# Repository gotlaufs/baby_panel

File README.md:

# baby_panel
Toy panel with a ton of lights and switches

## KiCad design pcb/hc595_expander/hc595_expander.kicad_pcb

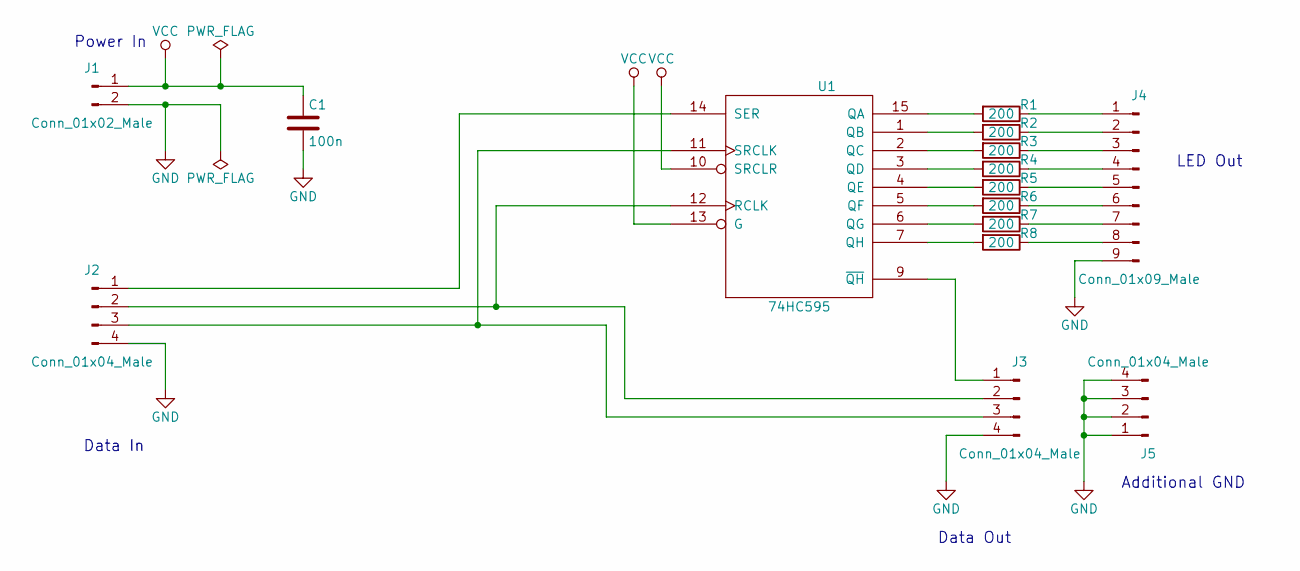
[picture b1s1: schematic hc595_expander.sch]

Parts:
C1: 100n; C_0805_HandSoldering
J1: Conn_01x02_Male; Header_1x02_2.54mm_Oval
J2, J3, J5: Conn_01x04_Male; Header_1x04_2.54mm_Oval
J4: Conn_01x09_Male; Header_1x09_2.54mm_Oval
R1, R2, R3, R4, R5, R6, R7, R8: 200; R_0805_HandSoldering
U1: 74HC595; SOIC-16W_7.5x10.3mm_Pitch1.27mm_HandSoldering

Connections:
GND: C1.2, J1.2, J2.4, J3.4, J4.9, J5.1, J5.2, J5.3, J5.4, U1.8 (GND)
unnamed: J2.1, U1.14 (SER)
unnamed: J2.2, J3.2, U1.12 (RCLK)
unnamed: J2.3, J3.3, U1.11 (SRCLK)
unnamed: J3.1, U1.9 (~QH)
unnamed: J4.1, R1.1
unnamed: J4.2, R2.1
unnamed: J4.3, R3.1
unnamed: J4.4, R4.1
unnamed: J4.5, R5.1
unnamed: J4.6, R6.1
unnamed: J4.7, R7.1
unnamed: J4.8, R8.1
unnamed: R1.2, U1.15 (QA)
unnamed: R2.2, U1.1 (QB)
unnamed: R3.2, U1.2 (QC)
unnamed: R4.2, U1.3 (QD)
unnamed: R5.2, U1.4 (QE)
unnamed: R6.2, U1.5 (QF)
unnamed: R7.2, U1.6 (QG)
unnamed: R8.2, U1.7 (QH)
VCC: C1.1, J1.1, U1.10 (SRCLR), U1.13 (G), U1.16 (VCC)

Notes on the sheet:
Power In
Data In
Data Out
Additional GND
LED Out

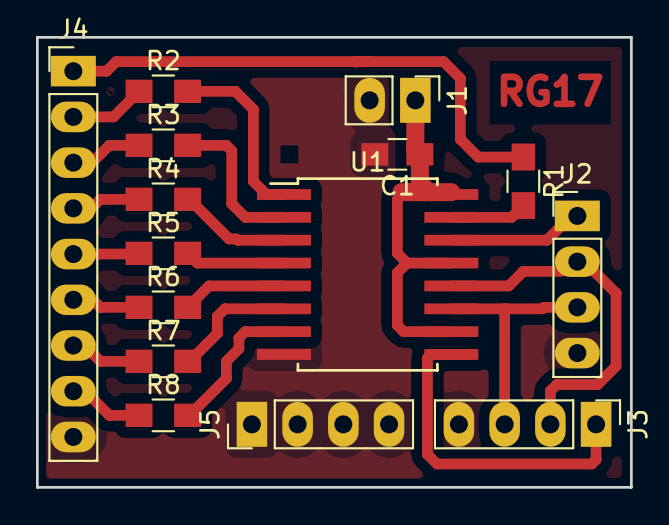
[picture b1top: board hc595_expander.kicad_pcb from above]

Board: 2 copper layers, 33.0 x 25.0 mm, 15 parts (0 on the bottom side), 22 nets.

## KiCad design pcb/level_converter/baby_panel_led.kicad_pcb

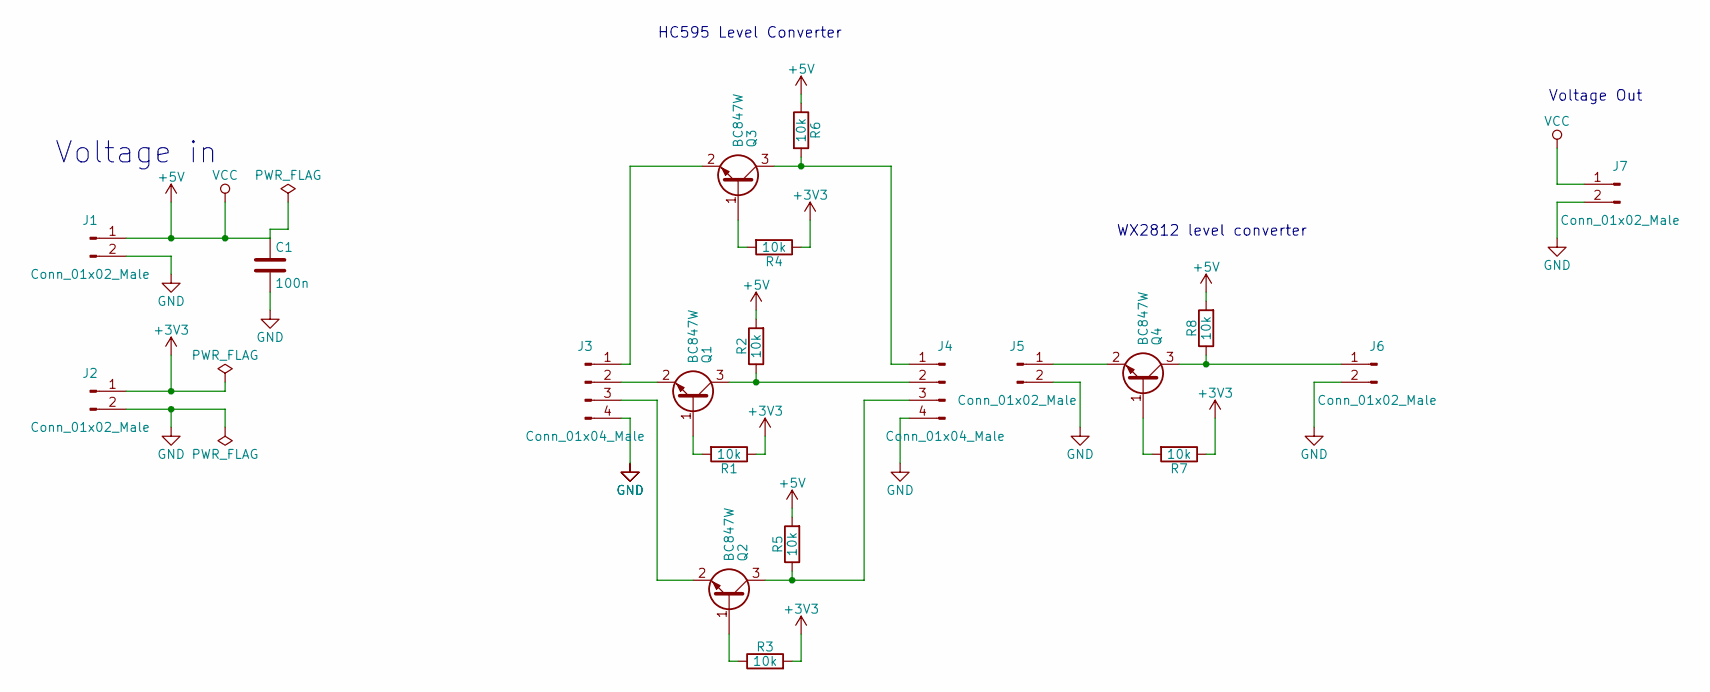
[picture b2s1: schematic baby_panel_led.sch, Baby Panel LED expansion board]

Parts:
C1: 100n; C_0805_HandSoldering
J1, J2, J5, J6, J7: Conn_01x02_Male; Header_1x02_2.54mm_Oval
J3, J4: Conn_01x04_Male; Header_1x04_2.54mm_Oval
Q1, Q2, Q3, Q4: BC847W; SOT-323_SC-70_Handsoldering
R1, R2, R3, R4, R5, R6, R7, R8: 10k; R_0805_HandSoldering

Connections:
+3V3: J2.1, R1.1, R3.2, R4.1, R7.1
+5V: C1.1, J1.1, J7.1, R2.2, R5.2, R6.1, R8.2
GND: C1.2, J1.2, J2.2, J3.4, J4.4, J5.2, J6.2, J7.2
unnamed: J3.1, Q3.2 (E)
unnamed: J3.2, Q1.2 (E)
unnamed: J3.3, Q2.2 (E)
unnamed: J4.1, Q3.3 (C), R6.2
unnamed: J4.2, Q1.3 (C), R2.1
unnamed: J4.3, Q2.3 (C), R5.1
unnamed: J5.1, Q4.2 (E)
unnamed: J6.1, Q4.3 (C), R8.1
unnamed: Q1.1 (B), R1.2
unnamed: Q2.1 (B), R3.1
unnamed: Q3.1 (B), R4.2
unnamed: Q4.1 (B), R7.2

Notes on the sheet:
Voltage in
WX2812 level converter
HC595 Level Converter
Voltage Out

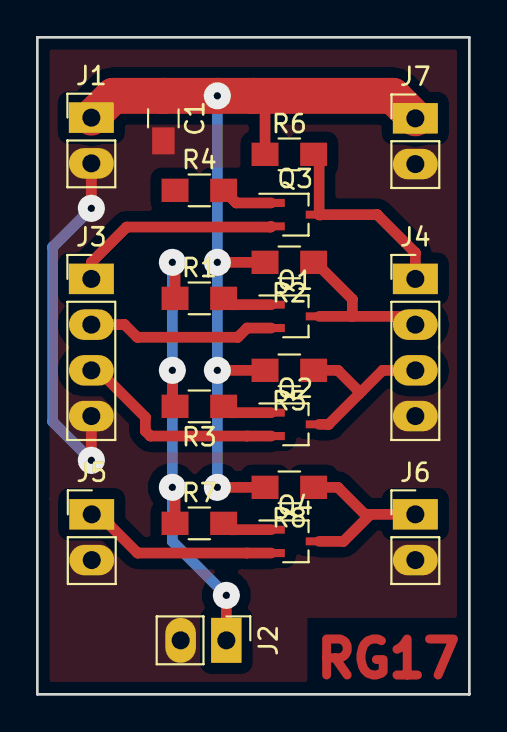
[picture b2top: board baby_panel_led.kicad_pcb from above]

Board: 2 copper layers, 24.0 x 36.5 mm, 20 parts (0 on the bottom side), 15 nets.

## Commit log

2017-12-26 Initial version
2017-12-26 Begin extracting animation logic from main to seperate functions
